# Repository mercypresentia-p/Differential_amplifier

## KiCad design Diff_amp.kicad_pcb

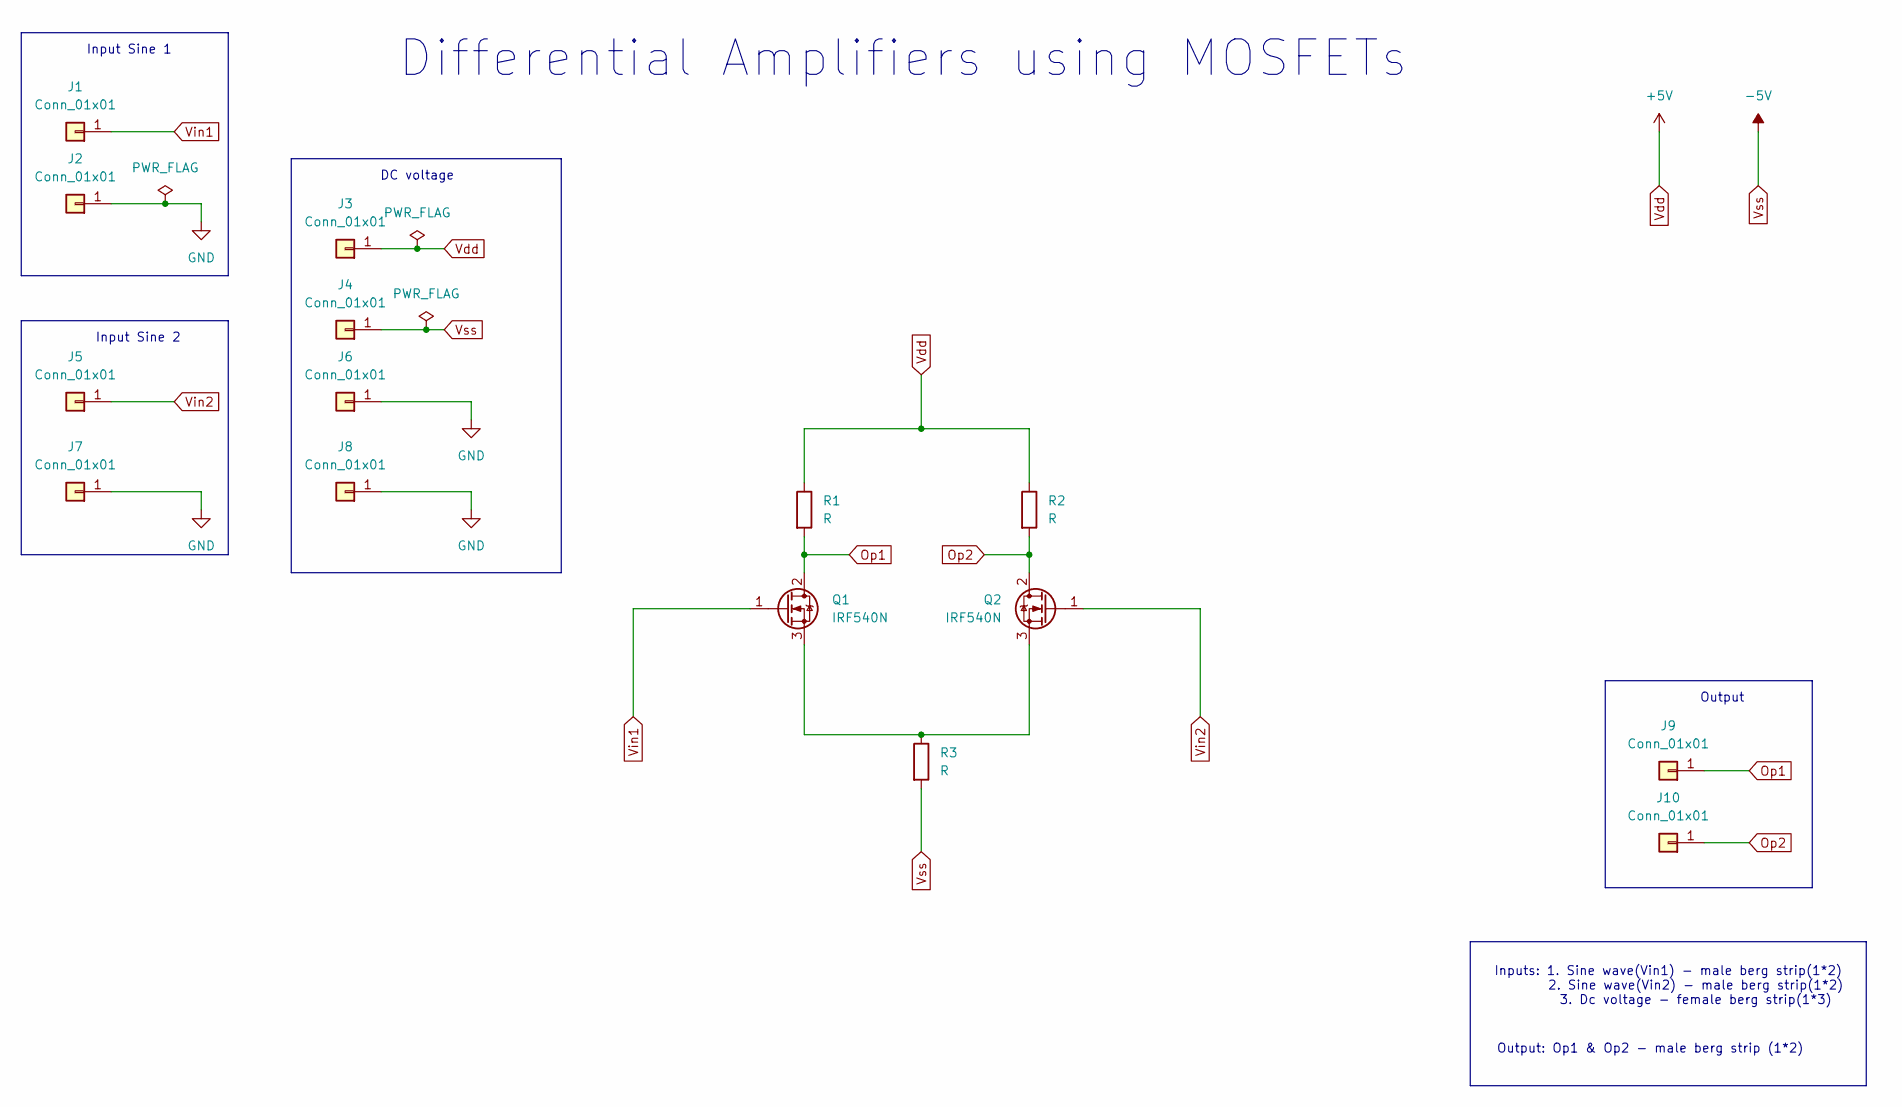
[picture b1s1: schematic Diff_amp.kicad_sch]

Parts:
J1, J2, J3, J4, J5, J6, J7, J8, J9, J10: Conn_01x01; PinHeader_1x01_P2.54mm_Vertical
Q1, Q2: IRF540N; TO-220-3_Vertical
R1, R2, R3: R; R_Axial_DIN0309_L9.0mm_D3.2mm_P15.24mm_Horizontal

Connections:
GND: J2.1 (Pin_1_1), J6.1 (Pin_1_1), J7.1 (Pin_1_1), J8.1 (Pin_1_1)
unnamed: Q1.3 (S), Q2.3 (S), R3.1
Op1: J9.1 (Pin_1_1), Q1.2 (D), R1.2
Op2: J10.1 (Pin_1_1), Q2.2 (D), R2.2
Vdd: J3.1 (Pin_1_1), R1.1, R2.1
Vin1: J1.1 (Pin_1_1), Q1.1 (G)
Vin2: J5.1 (Pin_1_1), Q2.1 (G)
Vss: J4.1 (Pin_1_1), R3.2

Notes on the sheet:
Inputs: 1. Sine wave(Vin1) - male berg strip(1*2) 2. Sine wave(Vin2) - male berg strip(1*2) 3. Dc voltage - female berg strip(1*3)
Differential Amplifiers using MOSFETs
Output
Output: Op1 & Op2 - male berg strip (1*2)
Input Sine 1
Input Sine 2
DC voltage

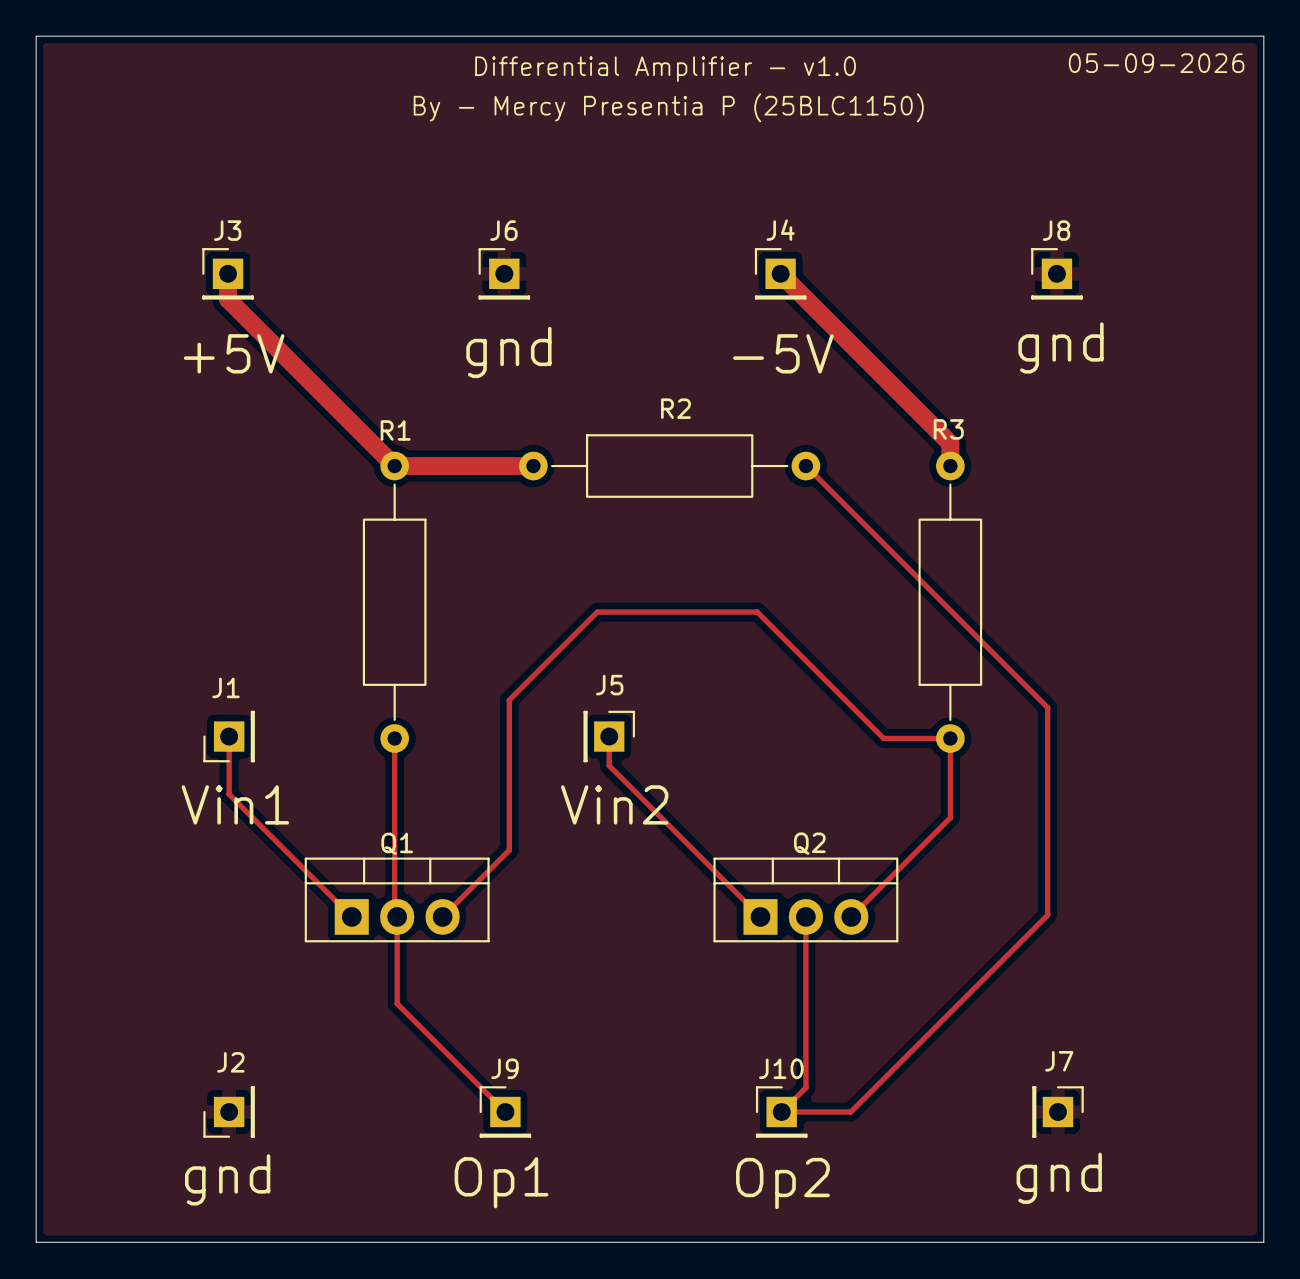
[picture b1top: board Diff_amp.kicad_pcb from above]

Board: 2 copper layers, 68.7 x 67.5 mm, 15 parts (0 on the bottom side), 8 nets.

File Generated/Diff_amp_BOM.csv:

"Reference","Qty","Value","DNP","Exclude from BOM","Exclude from Board","Footprint","Datasheet"
"J1,J2,J3,J4,J5,J6,J7,J8,J9,J10","10","Conn_01x01","","","","Connector_PinHeader_2.54mm:PinHeader_1x01_P2.54mm_Vertical",""
"Q1,Q2","2","IRF540N","","","","Package_TO_SOT_THT:TO-220-3_Vertical","http://www.irf.com/product-info/datasheets/data/irf540n.pdf"
"R1,R2,R3","3","R","","","","Resistor_THT:R_Axial_DIN0309_L9.0mm_D3.2mm_P15.24mm_Horizontal",""
